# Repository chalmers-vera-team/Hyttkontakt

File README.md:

# Hyttkontakt
Contact between the chassi's inside and outside. Using a Deutsch DT15-12PA and JST-EH (2.50 mm pitch). 

## Pinout 
1. 12V
2. Deadman 
3. Startmotor
4. Tachometer
5. Hallsensor
6. NC
7. TX
8. RX
9. Camera
10. Batteryrelay 12V
11. Batteryrelay 
12. GND

## Emergency stop rev 1.5
The emergency stop is inline with HMI and battery relay button. The power is going through the emergency button and back again to battery relay input and HMI. The HMI requires power directly from the battery and it is why this is done. 

## VISSS

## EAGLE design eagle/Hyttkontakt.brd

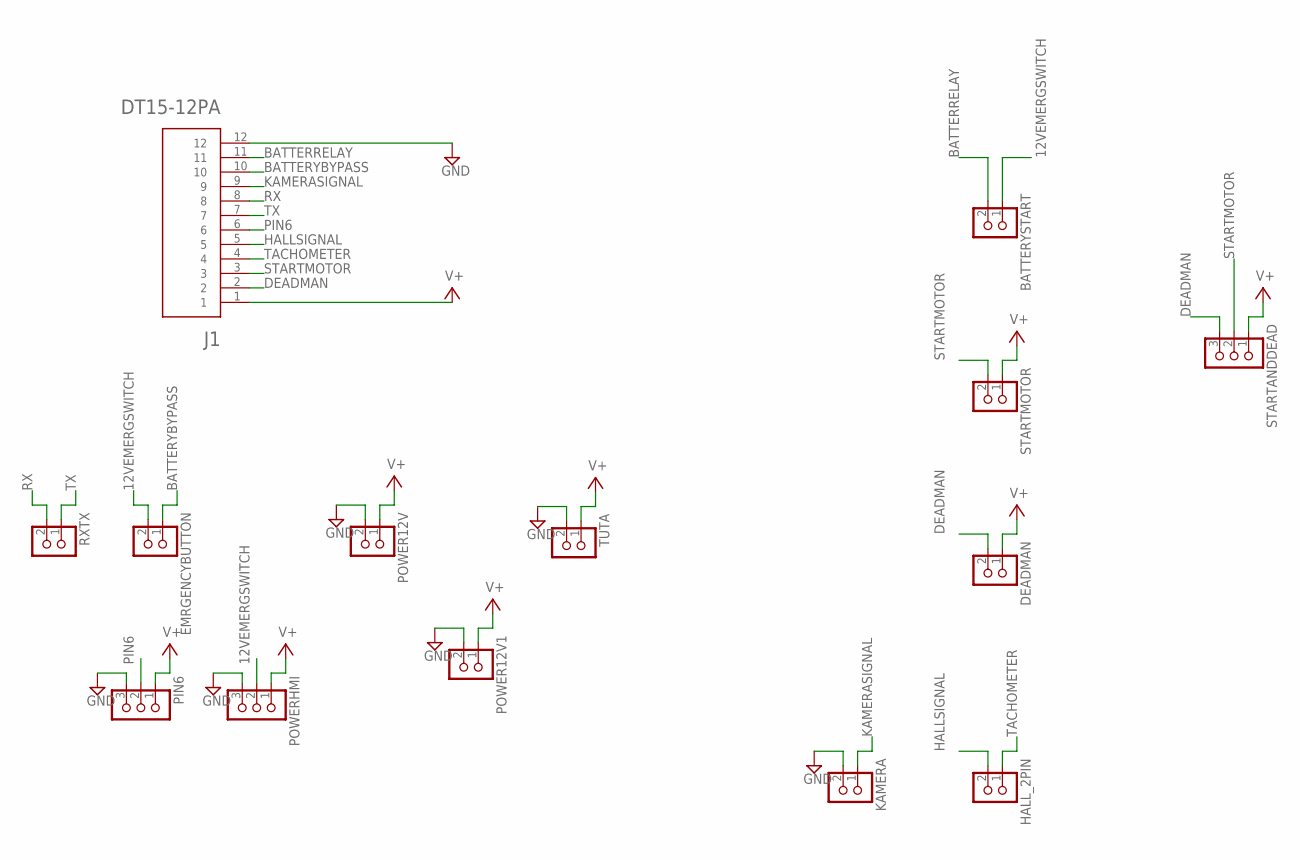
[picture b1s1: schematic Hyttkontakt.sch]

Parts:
BATTERYSTART: EH_B2B-EH; B2B-EH
DEADMAN: EH_B2B-EH; B2B-EH
EMRGENCYBUTTON: EH_B2B-EH; B2B-EH
HALL_2PIN: EH_B2B-EH; B2B-EH
J1: DT15-12PA; TE_DT15-12PA
KAMERA: EH_B2B-EH; B2B-EH
PIN6: EH_B3B-EH; B3B-EH
POWER12V, POWER12V1: EH_B2B-EH; B2B-EH
POWERHMI: EH_B3B-EH; B3B-EH
RXTX: EH_B2B-EH; B2B-EH
STARTANDDEAD: EH_B3B-EH; B3B-EH
STARTMOTOR: EH_B2B-EH; B2B-EH
TUTA: EH_B2B-EH; B2B-EH

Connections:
12VEMERGSWITCH: BATTERYSTART.1, EMRGENCYBUTTON.2, POWERHMI.2
BATTERRELAY: BATTERYSTART.2, J1.11
BATTERYBYPASS: EMRGENCYBUTTON.1, J1.10
DEADMAN: DEADMAN.2, J1.2, STARTANDDEAD.3
GND: J1.12, KAMERA.2, PIN6.3, POWER12V.2, POWER12V1.2, POWERHMI.3, TUTA.2
HALLSIGNAL: HALL_2PIN.2, J1.5
KAMERASIGNAL: J1.9, KAMERA.1
PIN6: J1.6, PIN6.2
RX: J1.8, RXTX.2
STARTMOTOR: J1.3, STARTANDDEAD.2, STARTMOTOR.2
TACHOMETER: HALL_2PIN.1, J1.4
TX: J1.7, RXTX.1
V+: DEADMAN.1, J1.1, PIN6.1, POWER12V.1, POWER12V1.1, POWERHMI.1, STARTANDDEAD.1, STARTMOTOR.1, TUTA.1

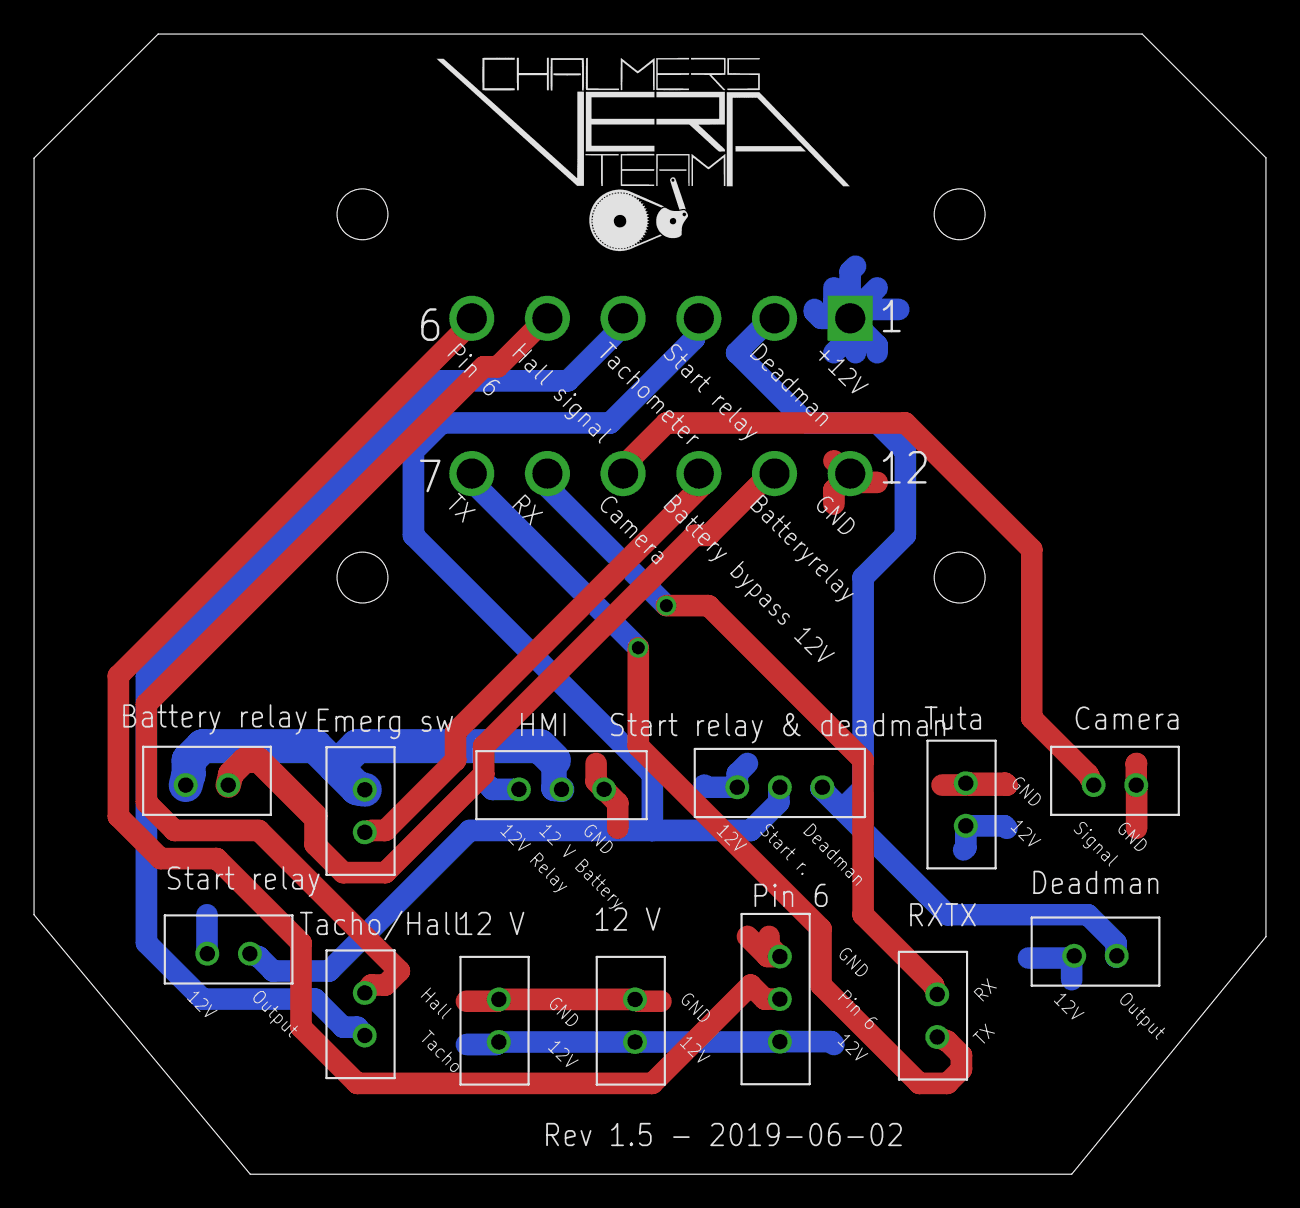
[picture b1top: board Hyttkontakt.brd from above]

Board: 2 copper layers, 72.4 x 67.0 mm, 14 parts (1 on the bottom side), 13 nets.

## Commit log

2019-03-24 Rev 1.4
2019-03-24 Updated layout (schematic)
    Just updated the layout in the schematic. More clean now
2019-03-24 Create Hyttkontakt.pdf
    Created an pdf from schematic
2019-03-24 Added cableholder
    Added a cableholder on the 3D printed adapter.
2019-03-24 Added cable strip hole
2019-03-25 Added hole for cable strip
2019-06-17 Bypass and easier connections
    - HMI now goes on batterybypass connection
    - Emergency button has its own connection in serie with HMI and Battery relay button
